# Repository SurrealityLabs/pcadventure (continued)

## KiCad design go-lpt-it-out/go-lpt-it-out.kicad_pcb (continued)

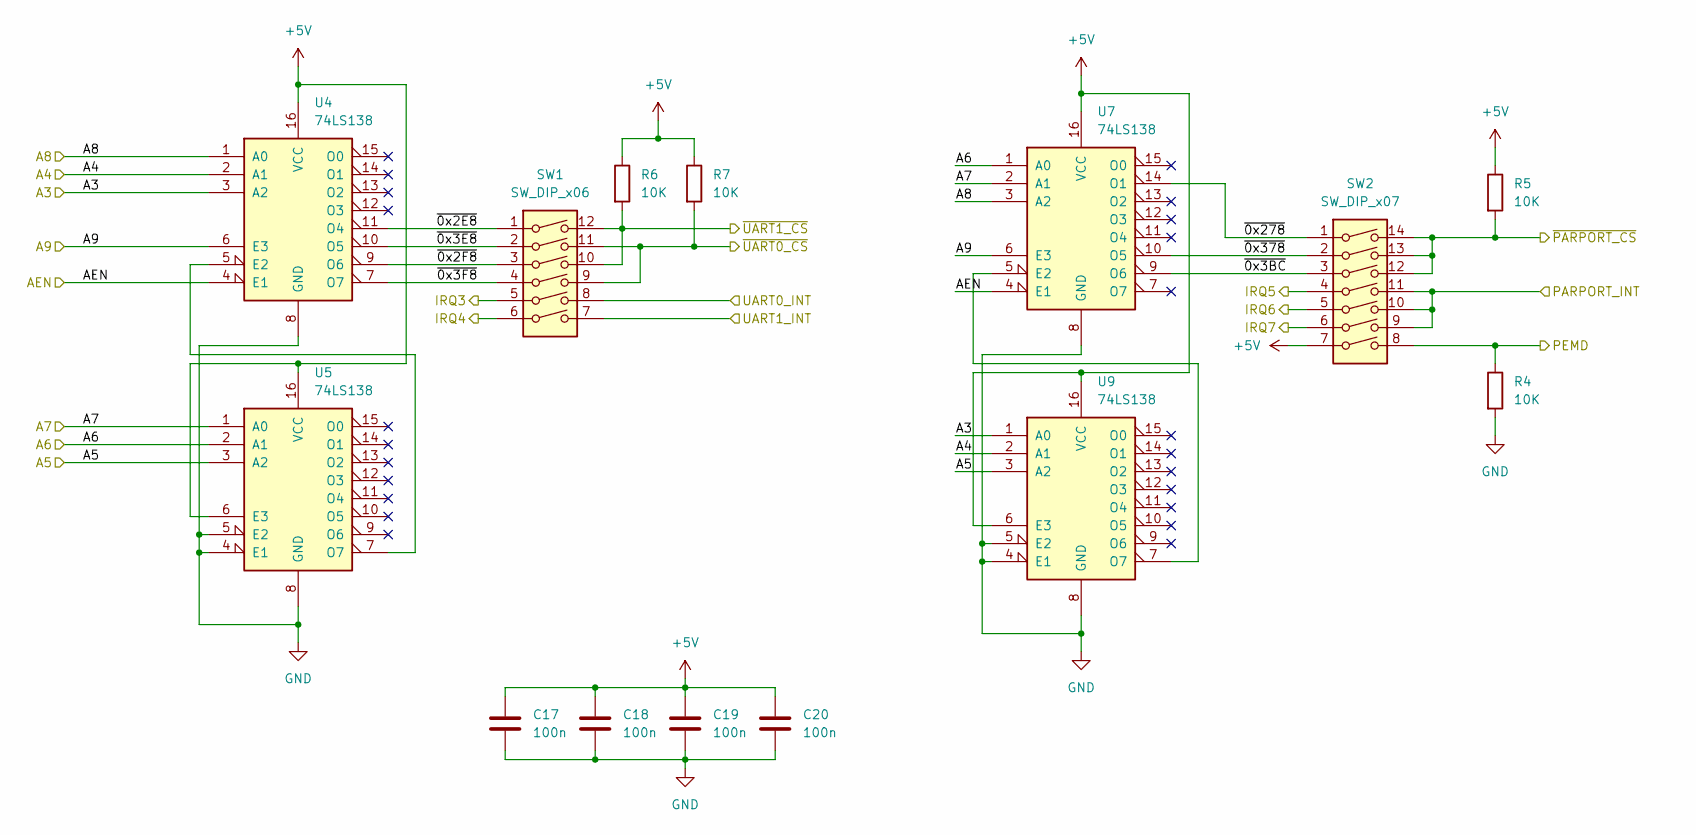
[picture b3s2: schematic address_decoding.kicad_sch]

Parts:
C17, C18, C19, C20: 100n; C_0603_1608Metric_Pad1.08x0.95mm_HandSolder
R4, R5, R6, R7: 10K; R_0603_1608Metric_Pad0.98x0.95mm_HandSolder
SW1: SW_DIP_x06; SW_DIP_SPSTx06_Slide_9.78x17.42mm_W7.62mm_P2.54mm
SW2: SW_DIP_x07; SW_DIP_SPSTx07_Slide_9.78x19.96mm_W7.62mm_P2.54mm
U4, U5, U7, U9: 74LS138; DIP-16_W7.62mm

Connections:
+5V: C17.1, C18.1, C19.1, C20.1, R5.1, R6.1, R7.1, SW2.7, U4.16 (VCC), U5.6 (E3), U5.16 (VCC), U7.16 (VCC), U9.6 (E3), U9.16 (VCC); also elsewhere on the board
/Address and Config/A3: U4.3 (A2), U9.1 (A0); also elsewhere on the board
/Address and Config/A4: U4.2 (A1), U9.2 (A1); also elsewhere on the board
/Address and Config/A5: U5.3 (A2), U9.3 (A2); also elsewhere on the board
/Address and Config/A6: U5.2 (A1), U7.1 (A0); also elsewhere on the board
/Address and Config/A7: U5.1 (A0), U7.2 (A1); also elsewhere on the board
/Address and Config/A8: U4.1 (A0), U7.3 (A2); also elsewhere on the board
/Address and Config/A9: U4.6 (E3), U7.6 (E3); also elsewhere on the board
/Address and Config/AEN: U4.4 (E1), U7.4 (E1); also elsewhere on the board
/Address and Config/PARPORT_INT: SW2.9, SW2.10, SW2.11; also elsewhere on the board
/Address and Config/PEMD: R4.1, SW2.8; also elsewhere on the board
/Address and Config/UART0_INT: SW1.8; also elsewhere on the board
/Address and Config/UART1_INT: SW1.7; also elsewhere on the board
/Address and Config/~0x2E8: SW1.1, U4.11 (O4)
/Address and Config/~0x2F8: SW1.3, U4.9 (O6)
/Address and Config/~0x3BC: SW2.3, U7.9 (O6)
/Address and Config/~0x3E8: SW1.2, U4.10 (O5)
/Address and Config/~0x3F8: SW1.4, U4.7 (O7)
/Address and Config/~0x278: SW2.1, U7.14 (O1)
/Address and Config/~0x378: SW2.2, U7.10 (O5)
/Address and Config/~PARPORT_CS: R5.2, SW2.12, SW2.13, SW2.14; also elsewhere on the board
/Address and Config/~UART0_CS: R7.2, SW1.9, SW1.11; also elsewhere on the board
/Address and Config/~UART1_CS: R6.2, SW1.10, SW1.12; also elsewhere on the board
/IRQ3: SW1.5; also elsewhere on the board
/IRQ4: SW1.6; also elsewhere on the board
/IRQ5: SW2.4; also elsewhere on the board
/IRQ6: SW2.5; also elsewhere on the board
/IRQ7: SW2.6; also elsewhere on the board
GND: C17.2, C18.2, C19.2, C20.2, R4.2, U4.8 (GND), U5.4 (E1), U5.5 (E2), U5.8 (GND), U7.8 (GND), U9.4 (E1), U9.5 (E2), U9.8 (GND); also elsewhere on the board
unnamed: U4.5 (E2), U5.7 (O7)
unnamed: U7.5 (E2), U9.7 (O7)

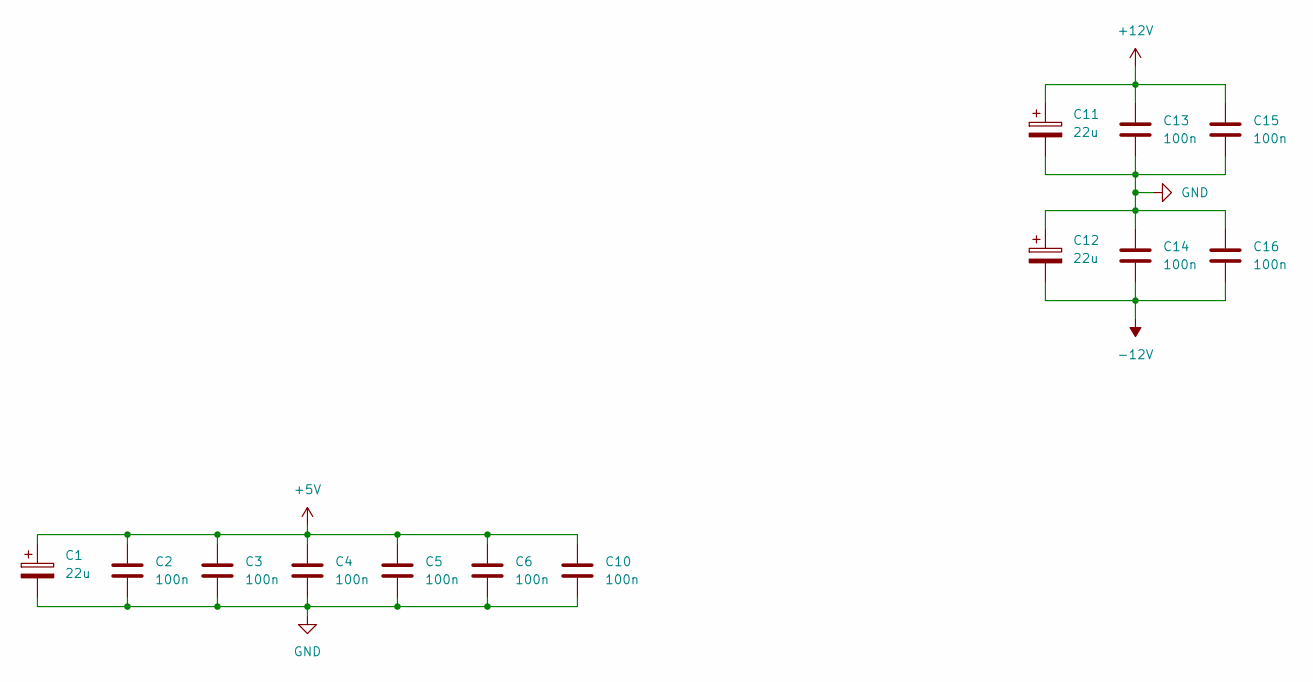
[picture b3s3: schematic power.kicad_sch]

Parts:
C1, C11, C12: 22u; CP_Elec_5x5.3
C2, C3, C4, C5, C6, C10, C13, C14, C15, C16: 100n; C_0603_1608Metric_Pad1.08x0.95mm_HandSolder

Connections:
+5V: C1.1, C2.1, C3.1, C4.1, C5.1, C6.1, C10.1; also elsewhere on the board
+12V: C11.1, C13.1, C15.1; also elsewhere on the board
-12V: C12.2, C14.2, C16.2; also elsewhere on the board
GND: C1.2, C2.2, C3.2, C4.2, C5.2, C6.2, C10.2, C11.2, C12.1, C13.2, C14.1, C15.2, C16.1; also elsewhere on the board

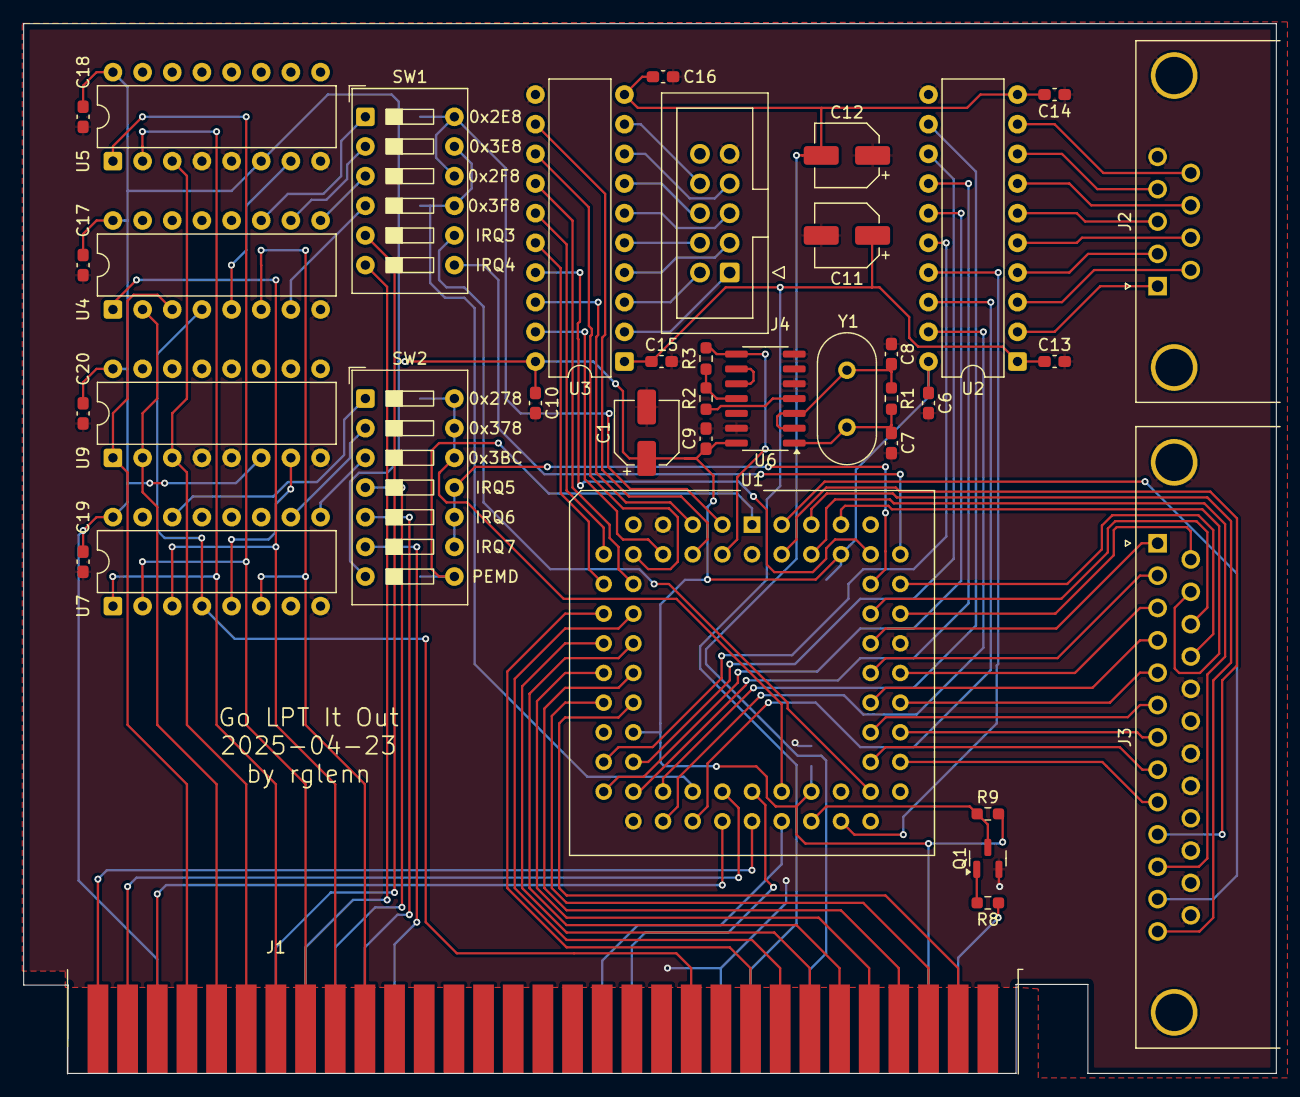
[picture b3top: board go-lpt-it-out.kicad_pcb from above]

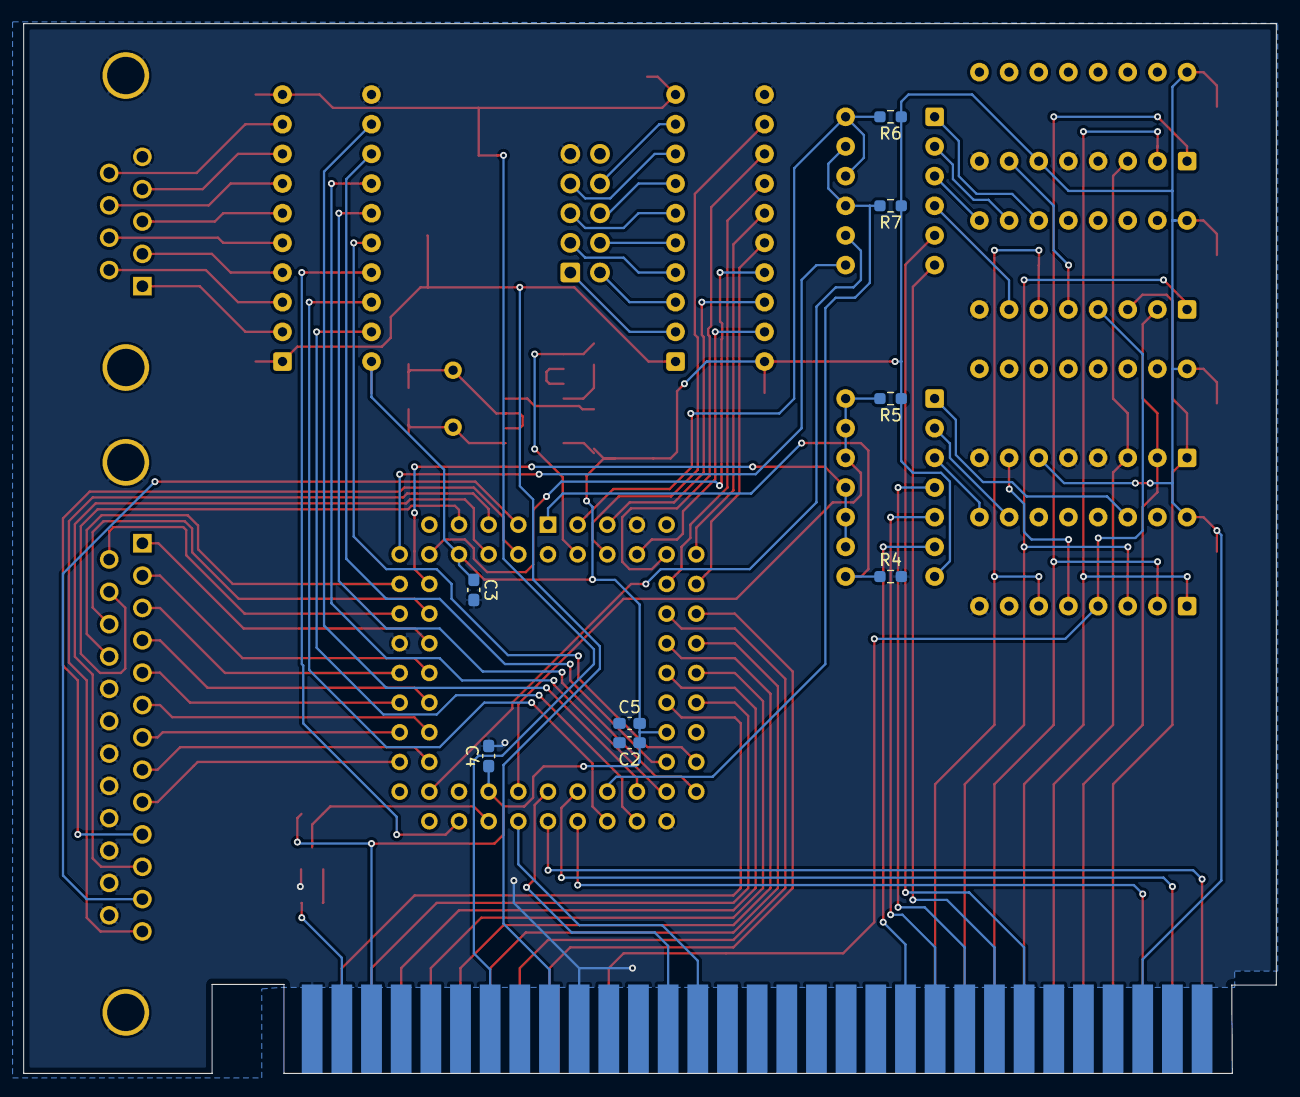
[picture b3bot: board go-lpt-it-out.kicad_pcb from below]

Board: 2 copper layers, 107.3 x 89.9 mm, 46 parts (8 on the bottom side), 104 nets.

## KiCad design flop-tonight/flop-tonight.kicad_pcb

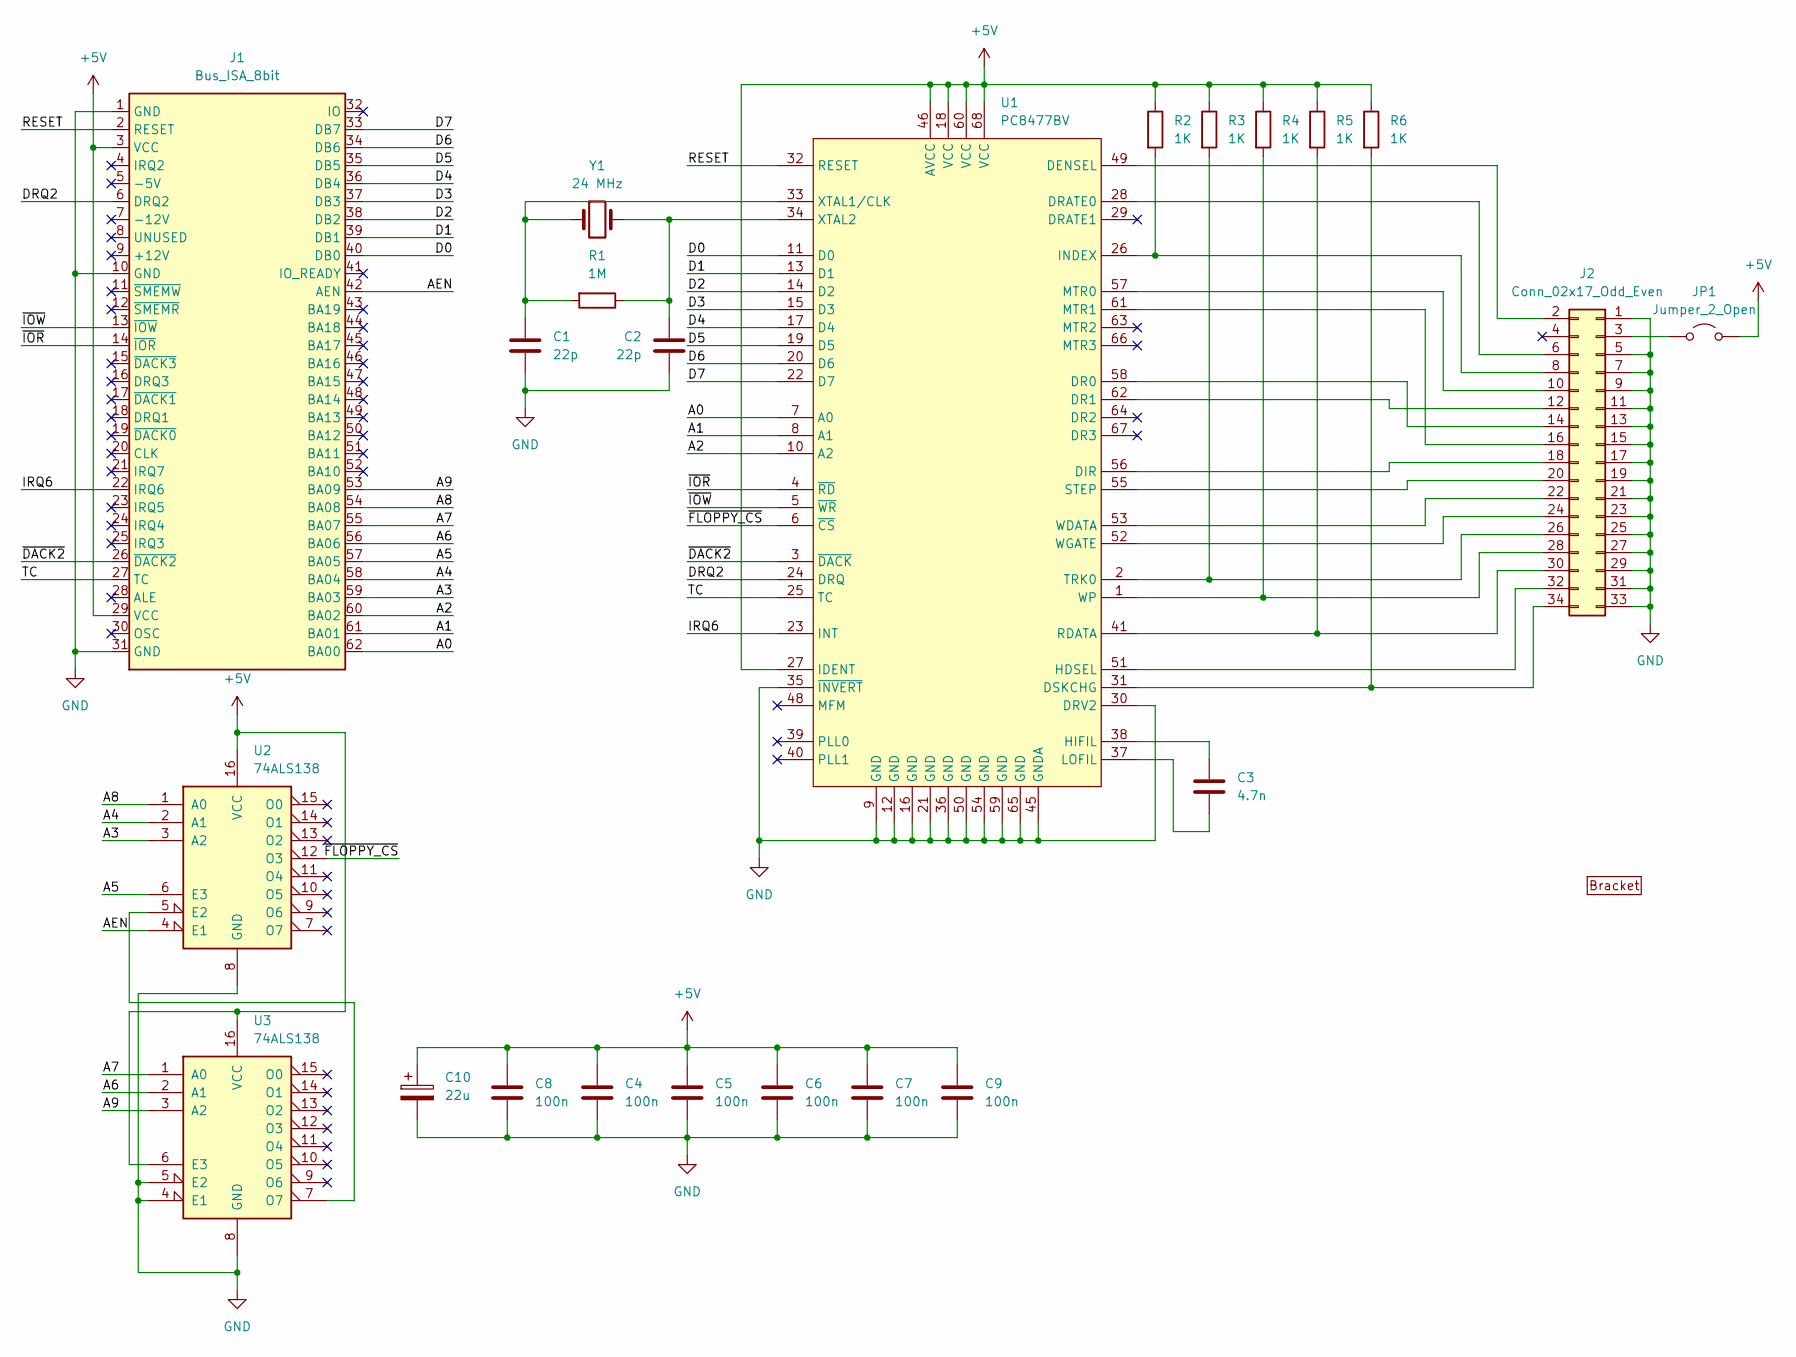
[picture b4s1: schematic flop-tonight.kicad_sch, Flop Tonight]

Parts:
BRACKET1: PC_BRACKET_ISA_KEYSTONE_9202_Rev1
C1, C2: 22p; C_0603_1608Metric_Pad1.08x0.95mm_HandSolder
C3: 4.7n; C_0603_1608Metric_Pad1.08x0.95mm_HandSolder
C4, C5, C6, C7, C8, C9: 100n; C_0603_1608Metric_Pad1.08x0.95mm_HandSolder
C10: 22u; CP_Elec_5x5.3
J1: Bus_ISA_8bit; BUS_AT_8BIT
J2: Conn_02x17_Odd_Even; IDC-Header_2x17_P2.54mm_Vertical
JP1: Jumper_2_Open; PinHeader_1x02_P2.54mm_Vertical
R1: 1M; R_0603_1608Metric_Pad0.98x0.95mm_HandSolder
R2, R3, R4, R5, R6: 1K; R_0603_1608Metric_Pad0.98x0.95mm_HandSolder
U1: PC8477BV; PLCC-68_THT-Socket
U2, U3: 74ALS138; DIP-16_W7.62mm
Y1: 24 MHz; Crystal_HC49-U_Vertical

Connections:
+5V: C4.1, C5.1, C6.1, C7.1, C8.1, C9.1, C10.1, J1.3 (VCC), J1.29 (VCC), JP1.2 (B), R2.1, R3.1, R4.1, R5.1, R6.1, U1.18 (VCC), U1.27 (IDENT), U1.46 (AVCC), U1.60 (VCC), U1.68 (VCC), U2.16 (VCC), U3.6 (E3), U3.16 (VCC)
/A0: J1.62 (BA00), U1.7 (A0)
/A1: J1.61 (BA01), U1.8 (A1)
/A2: J1.60 (BA02), U1.10 (A2)
/A3: J1.59 (BA03), U2.3 (A2)
/A4: J1.58 (BA04), U2.2 (A1)
/A5: J1.57 (BA05), U2.6 (E3)
/A6: J1.56 (BA06), U3.2 (A1)
/A7: J1.55 (BA07), U3.1 (A0)
/A8: J1.54 (BA08), U2.1 (A0)
/A9: J1.53 (BA09), U3.3 (A2)
/AEN: J1.42 (AEN), U2.4 (E1)
/D0: J1.40 (DB0), U1.11 (D0)
/D1: J1.39 (DB1), U1.13 (D1)
/D2: J1.38 (DB2), U1.14 (D2)
/D3: J1.37 (DB3), U1.15 (D3)
/D4: J1.36 (DB4), U1.17 (D4)
/D5: J1.35 (DB5), U1.19 (D5)
/D6: J1.34 (DB6), U1.20 (D6)
/D7: J1.33 (DB7), U1.22 (D7)
/DRQ2: J1.6 (DRQ2), U1.24 (DRQ)
/IRQ6: J1.22 (IRQ6), U1.23 (INT)
/RESET: J1.2 (RESET), U1.32 (RESET)
/TC: J1.27 (TC), U1.25 (TC)
/~DACK2: J1.26 (~DACK2), U1.3 (~DACK)
/~FLOPPY_CS: U1.6 (~CS), U2.12 (O3)
/~IOR: J1.14 (~IOR), U1.4 (~RD)
/~IOW: J1.13 (~IOW), U1.5 (~WR)
GND: C1.2, C2.2, C4.2, C5.2, C6.2, C7.2, C8.2, C9.2, C10.2, J1.1 (GND), J1.10 (GND), J1.31 (GND), J2.1, J2.5, J2.7, J2.9, J2.11, J2.13, J2.15, J2.17, J2.19, J2.21, J2.23, J2.25, J2.27, J2.29, J2.31, J2.33, U1.9 (GND), U1.12 (GND), U1.16 (GND), U1.21 (GND), U1.30 (DRV2), U1.35 (~INVERT), U1.36 (GND), U1.45 (GNDA), U1.50 (GND), U1.54 (GND), U1.59 (GND), U1.65 (GND), U2.8 (GND), U3.4 (E1), U3.5 (E2), U3.8 (GND)
unnamed: J2.2, U1.49 (DENSEL)
unnamed: J2.3, JP1.1 (A)
unnamed: J2.6, U1.28 (DRATE0)
unnamed: J2.8, R2.2, U1.26 (INDEX)
unnamed: J2.10, U1.57 (MTR0)
unnamed: J2.12, U1.62 (DR1)
unnamed: J2.14, U1.58 (DR0)
unnamed: J2.16, U1.61 (MTR1)
unnamed: J2.18, U1.56 (DIR)
unnamed: J2.20, U1.55 (STEP)
unnamed: J2.22, U1.53 (WDATA)
unnamed: J2.24, U1.52 (WGATE)
unnamed: J2.26, R3.2, U1.2 (TRK0)
unnamed: J2.28, R4.2, U1.1 (WP)
unnamed: J2.30, R5.2, U1.41 (RDATA)
unnamed: J2.32, U1.51 (HDSEL)
unnamed: J2.34, R6.2, U1.31 (DSKCHG)
unnamed: C3.1, U1.38 (HIFIL)
unnamed: C3.2, U1.37 (LOFIL)
unnamed: C1.1, R1.2, U1.33 (XTAL1/CLK), Y1.1
unnamed: C2.1, R1.1, U1.34 (XTAL2), Y1.2
unnamed: U2.5 (E2), U3.7 (O7)

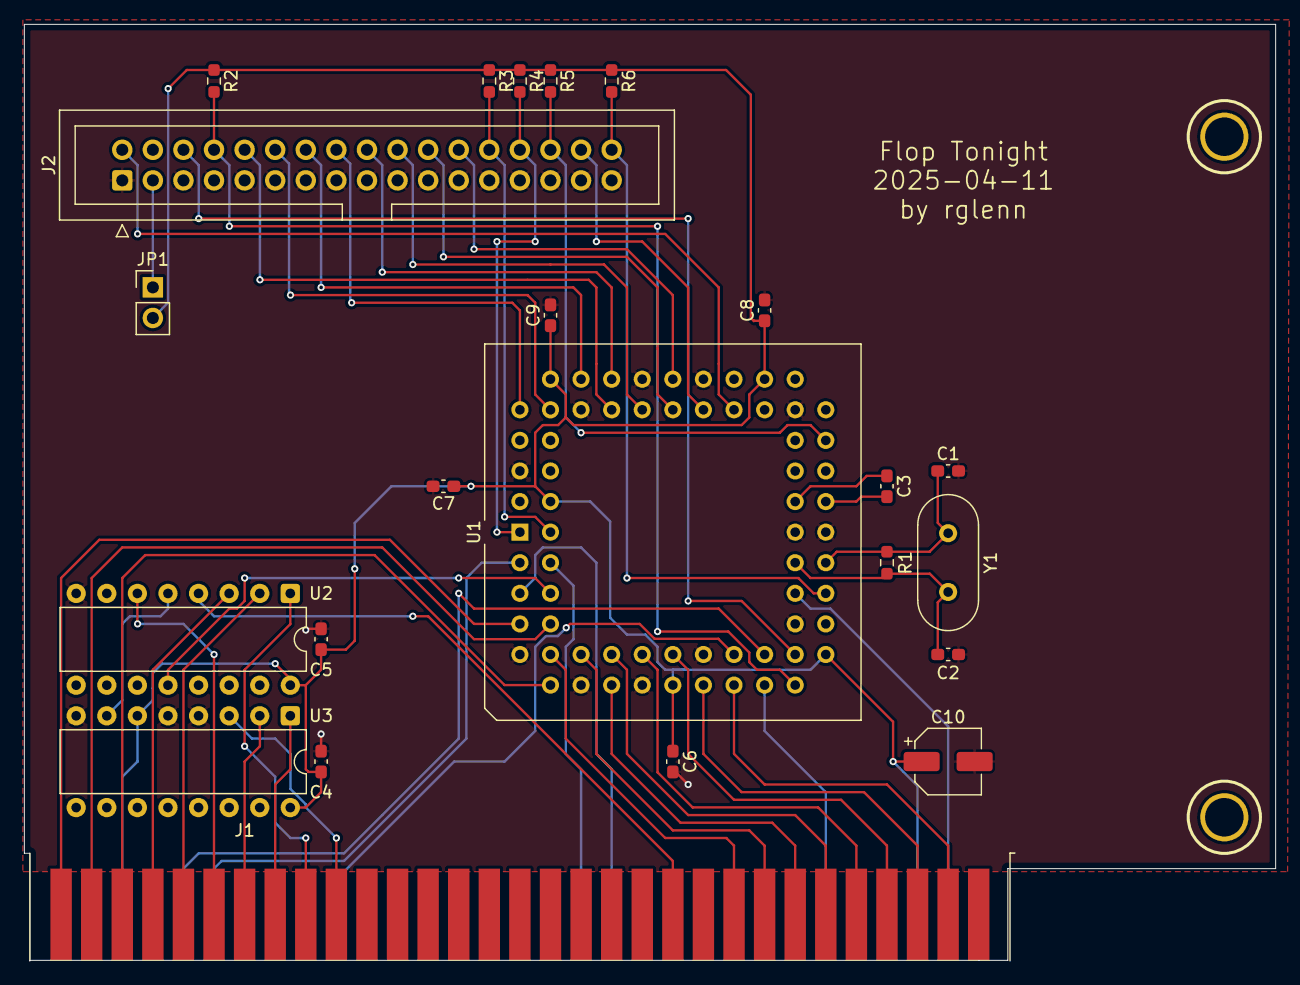
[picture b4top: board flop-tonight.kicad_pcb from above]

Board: 2 copper layers, 103.9 x 77.7 mm, 24 parts (0 on the bottom side), 51 nets.

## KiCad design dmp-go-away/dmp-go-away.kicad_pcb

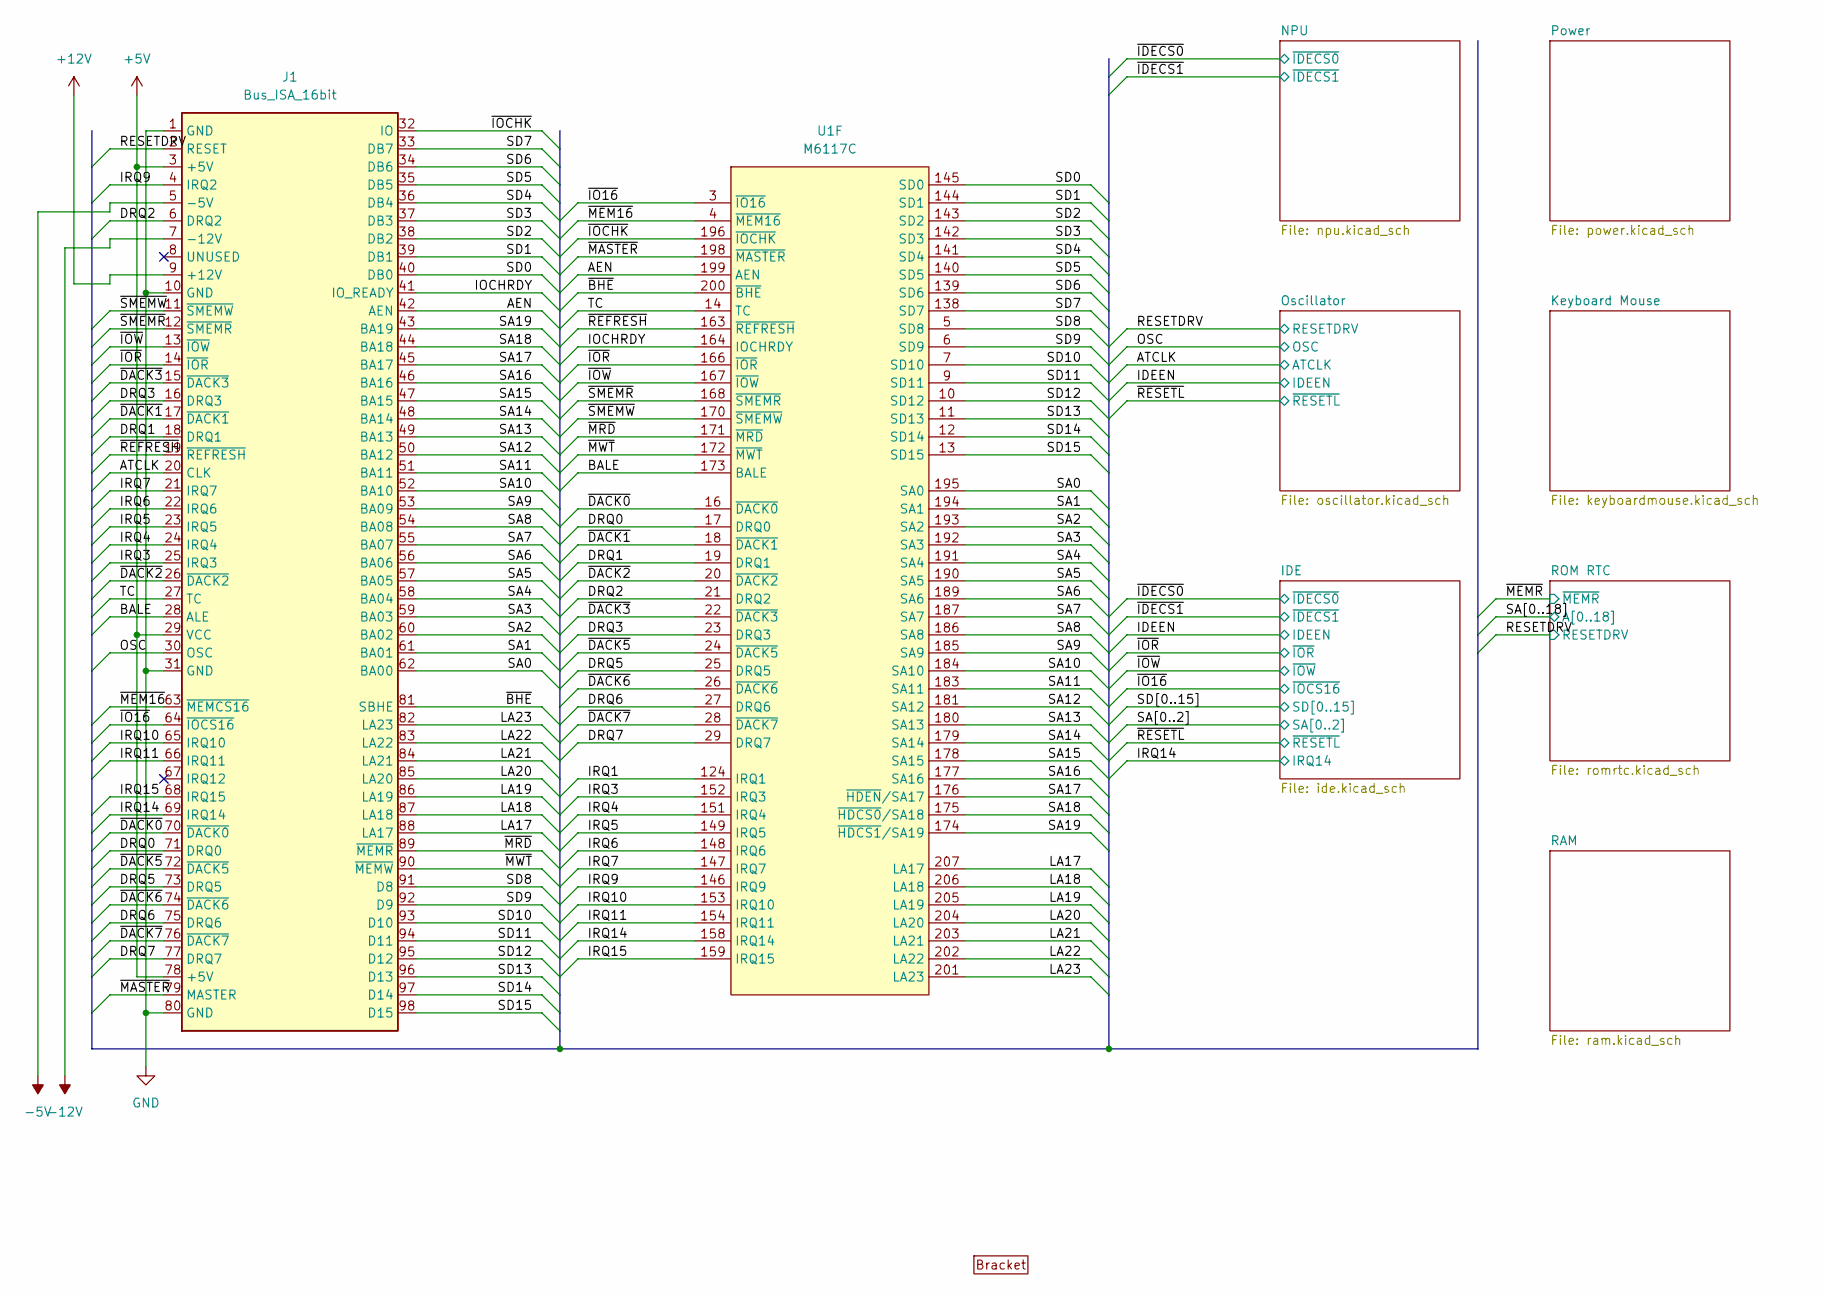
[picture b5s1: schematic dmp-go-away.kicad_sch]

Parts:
BRACKET1: PC_BRACKET_ISA_KEYSTONE_9202_Rev1
J1: Bus_ISA_16bit; BUS_AT
U1: M6117C; PQFP-208_28x28mm_P0.5mm

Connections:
+5V: J1.3 (+5V), J1.29 (VCC), J1.78 (+5V); also elsewhere on the board
+12V: J1.9 (+12V)
-5V: J1.5 (-5V)
-12V: J1.7 (-12V)
/AEN: J1.42 (AEN), U1.199 (AEN)
/ATCLK: J1.20 (CLK); also elsewhere on the board
/BALE: J1.28 (ALE), U1.173 (BALE)
/DRQ0: J1.71 (DRQ0), U1.17 (DRQ0)
/DRQ1: J1.18 (DRQ1), U1.19 (DRQ1)
/DRQ2: J1.6 (DRQ2), U1.21 (DRQ2)
/DRQ3: J1.16 (DRQ3), U1.23 (DRQ3)
/DRQ5: J1.73 (DRQ5), U1.25 (DRQ5)
/DRQ6: J1.75 (DRQ6), U1.27 (DRQ6)
/DRQ7: J1.77 (DRQ7), U1.29 (DRQ7)
/IOCHRDY: J1.41 (IO_READY), U1.164 (IOCHRDY)
/IRQ1: U1.124 (IRQ1)
/IRQ3: J1.25 (IRQ3), U1.152 (IRQ3)
/IRQ4: J1.24 (IRQ4), U1.151 (IRQ4)
/IRQ5: J1.23 (IRQ5), U1.149 (IRQ5)
/IRQ6: J1.22 (IRQ6), U1.148 (IRQ6)
/IRQ7: J1.21 (IRQ7), U1.147 (IRQ7)
/IRQ9: J1.4 (IRQ2), U1.146 (IRQ9)
/IRQ10: J1.65 (IRQ10), U1.153 (IRQ10)
/IRQ11: J1.66 (IRQ11), U1.154 (IRQ11)
/IRQ14: J1.69 (IRQ14), U1.158 (IRQ14); also elsewhere on the board
/IRQ15: J1.68 (IRQ15), U1.159 (IRQ15)
/LA17: J1.88 (LA17), U1.207 (LA17)
/LA18: J1.87 (LA18), U1.206 (LA18)
/LA19: J1.86 (LA19), U1.205 (LA19)
/LA20: J1.85 (LA20), U1.204 (LA20)
/LA21: J1.84 (LA21), U1.203 (LA21)
/LA22: J1.83 (LA22), U1.202 (LA22)
/LA23: J1.82 (LA23), U1.201 (LA23)
/OSC: J1.30 (OSC); also elsewhere on the board
/RESETDRV: J1.2 (RESET); also elsewhere on the board
/SA0: J1.62 (BA00), U1.195 (SA0); also elsewhere on the board
/SA1: J1.61 (BA01), U1.194 (SA1); also elsewhere on the board
/SA2: J1.60 (BA02), U1.193 (SA2); also elsewhere on the board
/SA3: J1.59 (BA03), U1.192 (SA3); also elsewhere on the board
/SA4: J1.58 (BA04), U1.191 (SA4); also elsewhere on the board
/SA5: J1.57 (BA05), U1.190 (SA5); also elsewhere on the board
/SA6: J1.56 (BA06), U1.189 (SA6); also elsewhere on the board
/SA7: J1.55 (BA07), U1.187 (SA7); also elsewhere on the board
/SA8: J1.54 (BA08), U1.186 (SA8); also elsewhere on the board
/SA9: J1.53 (BA09), U1.185 (SA9); also elsewhere on the board
/SA10: J1.52 (BA10), U1.184 (SA10); also elsewhere on the board
/SA11: J1.51 (BA11), U1.183 (SA11); also elsewhere on the board
/SA12: J1.50 (BA12), U1.181 (SA12); also elsewhere on the board
/SA13: J1.49 (BA13), U1.180 (SA13); also elsewhere on the board
/SA14: J1.48 (BA14), U1.179 (SA14); also elsewhere on the board
/SA15: J1.47 (BA15), U1.178 (SA15); also elsewhere on the board
/SA16: J1.46 (BA16), U1.177 (SA16); also elsewhere on the board
/SA17: J1.45 (BA17), U1.176 (~HDEN/SA17); also elsewhere on the board
/SA18: J1.44 (BA18), U1.175 (~HDCS0/SA18); also elsewhere on the board
/SA19: J1.43 (BA19), U1.174 (~HDCS1/SA19)
/SD0: J1.40 (DB0), U1.145 (SD0); also elsewhere on the board
/SD1: J1.39 (DB1), U1.144 (SD1); also elsewhere on the board
/SD2: J1.38 (DB2), U1.143 (SD2); also elsewhere on the board
/SD3: J1.37 (DB3), U1.142 (SD3); also elsewhere on the board
/SD4: J1.36 (DB4), U1.141 (SD4); also elsewhere on the board
/SD5: J1.35 (DB5), U1.140 (SD5); also elsewhere on the board
/SD6: J1.34 (DB6), U1.139 (SD6); also elsewhere on the board
/SD7: J1.33 (DB7), U1.138 (SD7); also elsewhere on the board
/SD8: J1.91 (D8), U1.5 (SD8); also elsewhere on the board
/SD9: J1.92 (D9), U1.6 (SD9); also elsewhere on the board
/SD10: J1.93 (D10), U1.7 (SD10); also elsewhere on the board
/SD11: J1.94 (D11), U1.9 (SD11); also elsewhere on the board
/SD12: J1.95 (D12), U1.10 (SD12); also elsewhere on the board
/SD13: J1.96 (D13), U1.11 (SD13); also elsewhere on the board
/SD14: J1.97 (D14), U1.12 (SD14); also elsewhere on the board
/SD15: J1.98 (D15), U1.13 (SD15); also elsewhere on the board
/TC: J1.27 (TC), U1.14 (TC)
/~BHE: J1.81 (SBHE), U1.200 (~BHE)
/~DACK0: J1.70 (~DACK0), U1.16 (~DACK0)
/~DACK1: J1.17 (~DACK1), U1.18 (~DACK1)
/~DACK2: J1.26 (~DACK2), U1.20 (~DACK2)
/~DACK3: J1.15 (~DACK3), U1.22 (~DACK3)
/~DACK5: J1.72 (~DACK5), U1.24 (~DACK5)
/~DACK6: J1.74 (~DACK6), U1.26 (~DACK6)
/~DACK7: J1.76 (~DACK7), U1.28 (~DACK7)
/~IO16: J1.64 (~IOCS16), U1.3 (~IO16); also elsewhere on the board
/~IOCHK: J1.32 (IO), U1.196 (~IOCHK)
/~IOR: J1.14 (~IOR), U1.166 (~IOR); also elsewhere on the board
/~IOW: J1.13 (~IOW), U1.167 (~IOW); also elsewhere on the board
/~MASTER: J1.79 (MASTER), U1.198 (~MASTER)
/~MEM16: J1.63 (~MEMCS16), U1.4 (~MEM16)
/~MRD: J1.89 (~MEMR), U1.171 (~MRD)
/~MWT: J1.90 (~MEMW), U1.172 (~MWT)
/~REFRESH: J1.19 (~REFRESH), U1.163 (~REFRESH)
/~SMEMR: J1.12 (~SMEMR), U1.168 (~SMEMR)
/~SMEMW: J1.11 (~SMEMW), U1.170 (~SMEMW)
GND: J1.1 (GND), J1.10 (GND), J1.31 (GND), J1.80 (GND); also elsewhere on the board

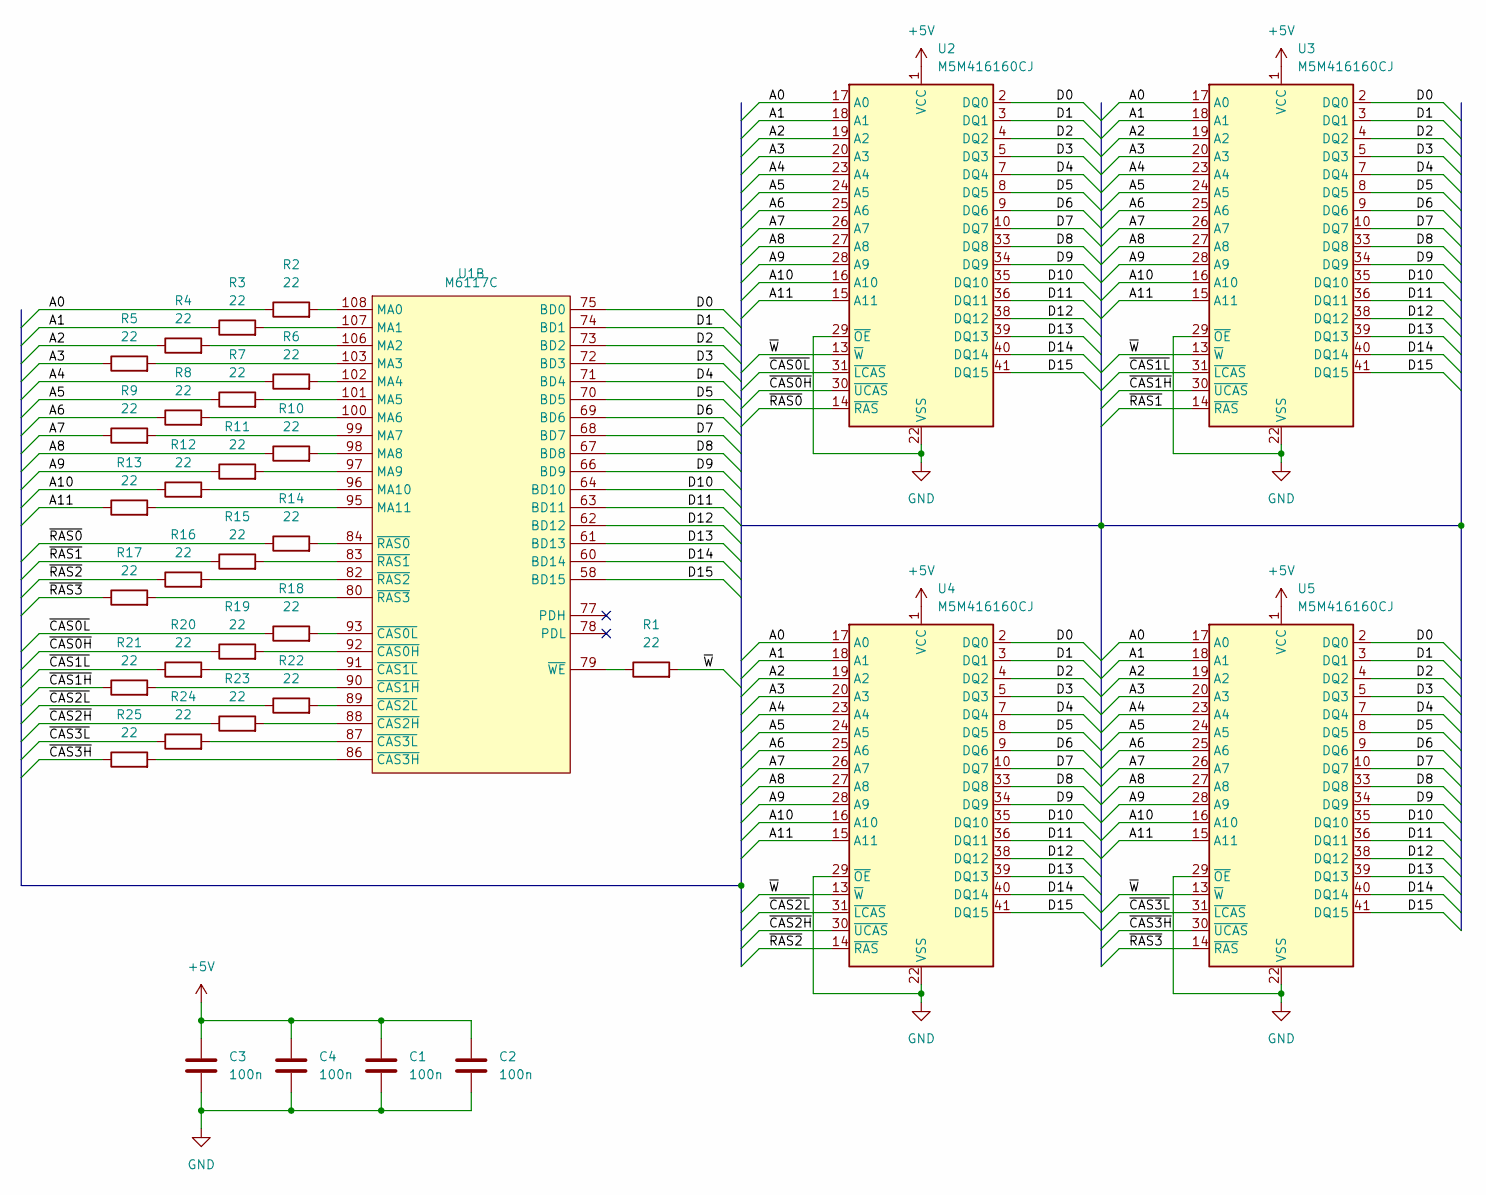
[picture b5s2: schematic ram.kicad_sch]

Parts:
C1, C2, C3, C4: 100n; C_0603_1608Metric_Pad1.08x0.95mm_HandSolder
R1, R2, R3, R4, R5, R6, R7, R8, R9, R10, R11, R12, R13, R14, R15, R16, R17, R18, R19, R20, R21, R22, R23, R24, R25: 22; R_0603_1608Metric_Pad0.98x0.95mm_HandSolder
U1: M6117C; PQFP-208_28x28mm_P0.5mm
U2, U3, U4, U5: M5M416160CJ; SOJ-42

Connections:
+5V: C1.1, C2.1, C3.1, C4.1, U2.1 (VCC), U2.6 (VCC), U2.21 (VCC), U3.1 (VCC), U3.6 (VCC), U3.21 (VCC), U4.1 (VCC), U4.6 (VCC), U4.21 (VCC), U5.1 (VCC), U5.6 (VCC), U5.21 (VCC); also elsewhere on the board
/RAM/A0: R2.1, U2.17 (A0), U3.17 (A0), U4.17 (A0), U5.17 (A0)
/RAM/A1: R3.1, U2.18 (A1), U3.18 (A1), U4.18 (A1), U5.18 (A1)
/RAM/A2: R4.1, U2.19 (A2), U3.19 (A2), U4.19 (A2), U5.19 (A2)
/RAM/A3: R5.1, U2.20 (A3), U3.20 (A3), U4.20 (A3), U5.20 (A3)
/RAM/A4: R6.1, U2.23 (A4), U3.23 (A4), U4.23 (A4), U5.23 (A4)
/RAM/A5: R7.1, U2.24 (A5), U3.24 (A5), U4.24 (A5), U5.24 (A5)
/RAM/A6: R8.1, U2.25 (A6), U3.25 (A6), U4.25 (A6), U5.25 (A6)
/RAM/A7: R9.1, U2.26 (A7), U3.26 (A7), U4.26 (A7), U5.26 (A7)
/RAM/A8: R10.1, U2.27 (A8), U3.27 (A8), U4.27 (A8), U5.27 (A8)
/RAM/A9: R11.1, U2.28 (A9), U3.28 (A9), U4.28 (A9), U5.28 (A9)
/RAM/A10: R12.1, U2.16 (A10), U3.16 (A10), U4.16 (A10), U5.16 (A10)
/RAM/A11: R13.1, U2.15 (A11), U3.15 (A11), U4.15 (A11), U5.15 (A11)
/RAM/D0: U1.75 (BD0), U2.2 (DQ0), U3.2 (DQ0), U4.2 (DQ0), U5.2 (DQ0)
/RAM/D1: U1.74 (BD1), U2.3 (DQ1), U3.3 (DQ1), U4.3 (DQ1), U5.3 (DQ1)
/RAM/D2: U1.73 (BD2), U2.4 (DQ2), U3.4 (DQ2), U4.4 (DQ2), U5.4 (DQ2)
/RAM/D3: U1.72 (BD3), U2.5 (DQ3), U3.5 (DQ3), U4.5 (DQ3), U5.5 (DQ3)
/RAM/D4: U1.71 (BD4), U2.7 (DQ4), U3.7 (DQ4), U4.7 (DQ4), U5.7 (DQ4)
/RAM/D5: U1.70 (BD5), U2.8 (DQ5), U3.8 (DQ5), U4.8 (DQ5), U5.8 (DQ5)
/RAM/D6: U1.69 (BD6), U2.9 (DQ6), U3.9 (DQ6), U4.9 (DQ6), U5.9 (DQ6)
/RAM/D7: U1.68 (BD7), U2.10 (DQ7), U3.10 (DQ7), U4.10 (DQ7), U5.10 (DQ7)
/RAM/D8: U1.67 (BD8), U2.33 (DQ8), U3.33 (DQ8), U4.33 (DQ8), U5.33 (DQ8)
/RAM/D9: U1.66 (BD9), U2.34 (DQ9), U3.34 (DQ9), U4.34 (DQ9), U5.34 (DQ9)
/RAM/D10: U1.64 (BD10), U2.35 (DQ10), U3.35 (DQ10), U4.35 (DQ10), U5.35 (DQ10)
/RAM/D11: U1.63 (BD11), U2.36 (DQ11), U3.36 (DQ11), U4.36 (DQ11), U5.36 (DQ11)
/RAM/D12: U1.62 (BD12), U2.38 (DQ12), U3.38 (DQ12), U4.38 (DQ12), U5.38 (DQ12)
/RAM/D13: U1.61 (BD13), U2.39 (DQ13), U3.39 (DQ13), U4.39 (DQ13), U5.39 (DQ13)
/RAM/D14: U1.60 (BD14), U2.40 (DQ14), U3.40 (DQ14), U4.40 (DQ14), U5.40 (DQ14)
/RAM/D15: U1.58 (BD15), U2.41 (DQ15), U3.41 (DQ15), U4.41 (DQ15), U5.41 (DQ15)
/RAM/~CAS0H: R19.1, U2.30 (~UCAS)
/RAM/~CAS0L: R18.1, U2.31 (~LCAS)
/RAM/~CAS1H: R21.1, U3.30 (~UCAS)
/RAM/~CAS1L: R20.1, U3.31 (~LCAS)
/RAM/~CAS2H: R23.1, U4.30 (~UCAS)
/RAM/~CAS2L: R22.1, U4.31 (~LCAS)
/RAM/~CAS3H: R25.1, U5.30 (~UCAS)
/RAM/~CAS3L: R24.1, U5.31 (~LCAS)
/RAM/~RAS0: R14.1, U2.14 (~RAS)
/RAM/~RAS1: R15.1, U3.14 (~RAS)
/RAM/~RAS2: R16.1, U4.14 (~RAS)
/RAM/~RAS3: R17.1, U5.14 (~RAS)
/RAM/~W: R1.2, U2.13 (~W), U3.13 (~W), U4.13 (~W), U5.13 (~W)
GND: C1.2, C2.2, C3.2, C4.2, U2.22 (VSS), U2.29 (~OE), U2.37 (VSS), U2.42 (VSS), U3.22 (VSS), U3.29 (~OE), U3.37 (VSS), U3.42 (VSS), U4.22 (VSS), U4.29 (~OE), U4.37 (VSS), U4.42 (VSS), U5.22 (VSS), U5.29 (~OE), U5.37 (VSS), U5.42 (VSS); also elsewhere on the board
unnamed: R2.2, U1.108 (MA0)
unnamed: R3.2, U1.107 (MA1)
unnamed: R4.2, U1.106 (MA2)
unnamed: R5.2, U1.103 (MA3)
unnamed: R6.2, U1.102 (MA4)
unnamed: R7.2, U1.101 (MA5)
unnamed: R8.2, U1.100 (MA6)
unnamed: R9.2, U1.99 (MA7)
unnamed: R10.2, U1.98 (MA8)
unnamed: R11.2, U1.97 (MA9)
unnamed: R12.2, U1.96 (MA10)
unnamed: R13.2, U1.95 (MA11)
unnamed: R19.2, U1.92 (~CAS0H)
unnamed: R18.2, U1.93 (~CAS0L)
unnamed: R21.2, U1.90 (~CAS1H)
unnamed: R20.2, U1.91 (~CAS1L)
unnamed: R23.2, U1.88 (~CAS2H)
unnamed: R22.2, U1.89 (~CAS2L)
unnamed: R25.2, U1.86 (~CAS3H)
unnamed: R24.2, U1.87 (~CAS3L)
unnamed: R14.2, U1.84 (~RAS0)
unnamed: R15.2, U1.83 (~RAS1)
unnamed: R16.2, U1.82 (~RAS2)
unnamed: R17.2, U1.80 (~RAS3)
unnamed: R1.1, U1.79 (~WE)
